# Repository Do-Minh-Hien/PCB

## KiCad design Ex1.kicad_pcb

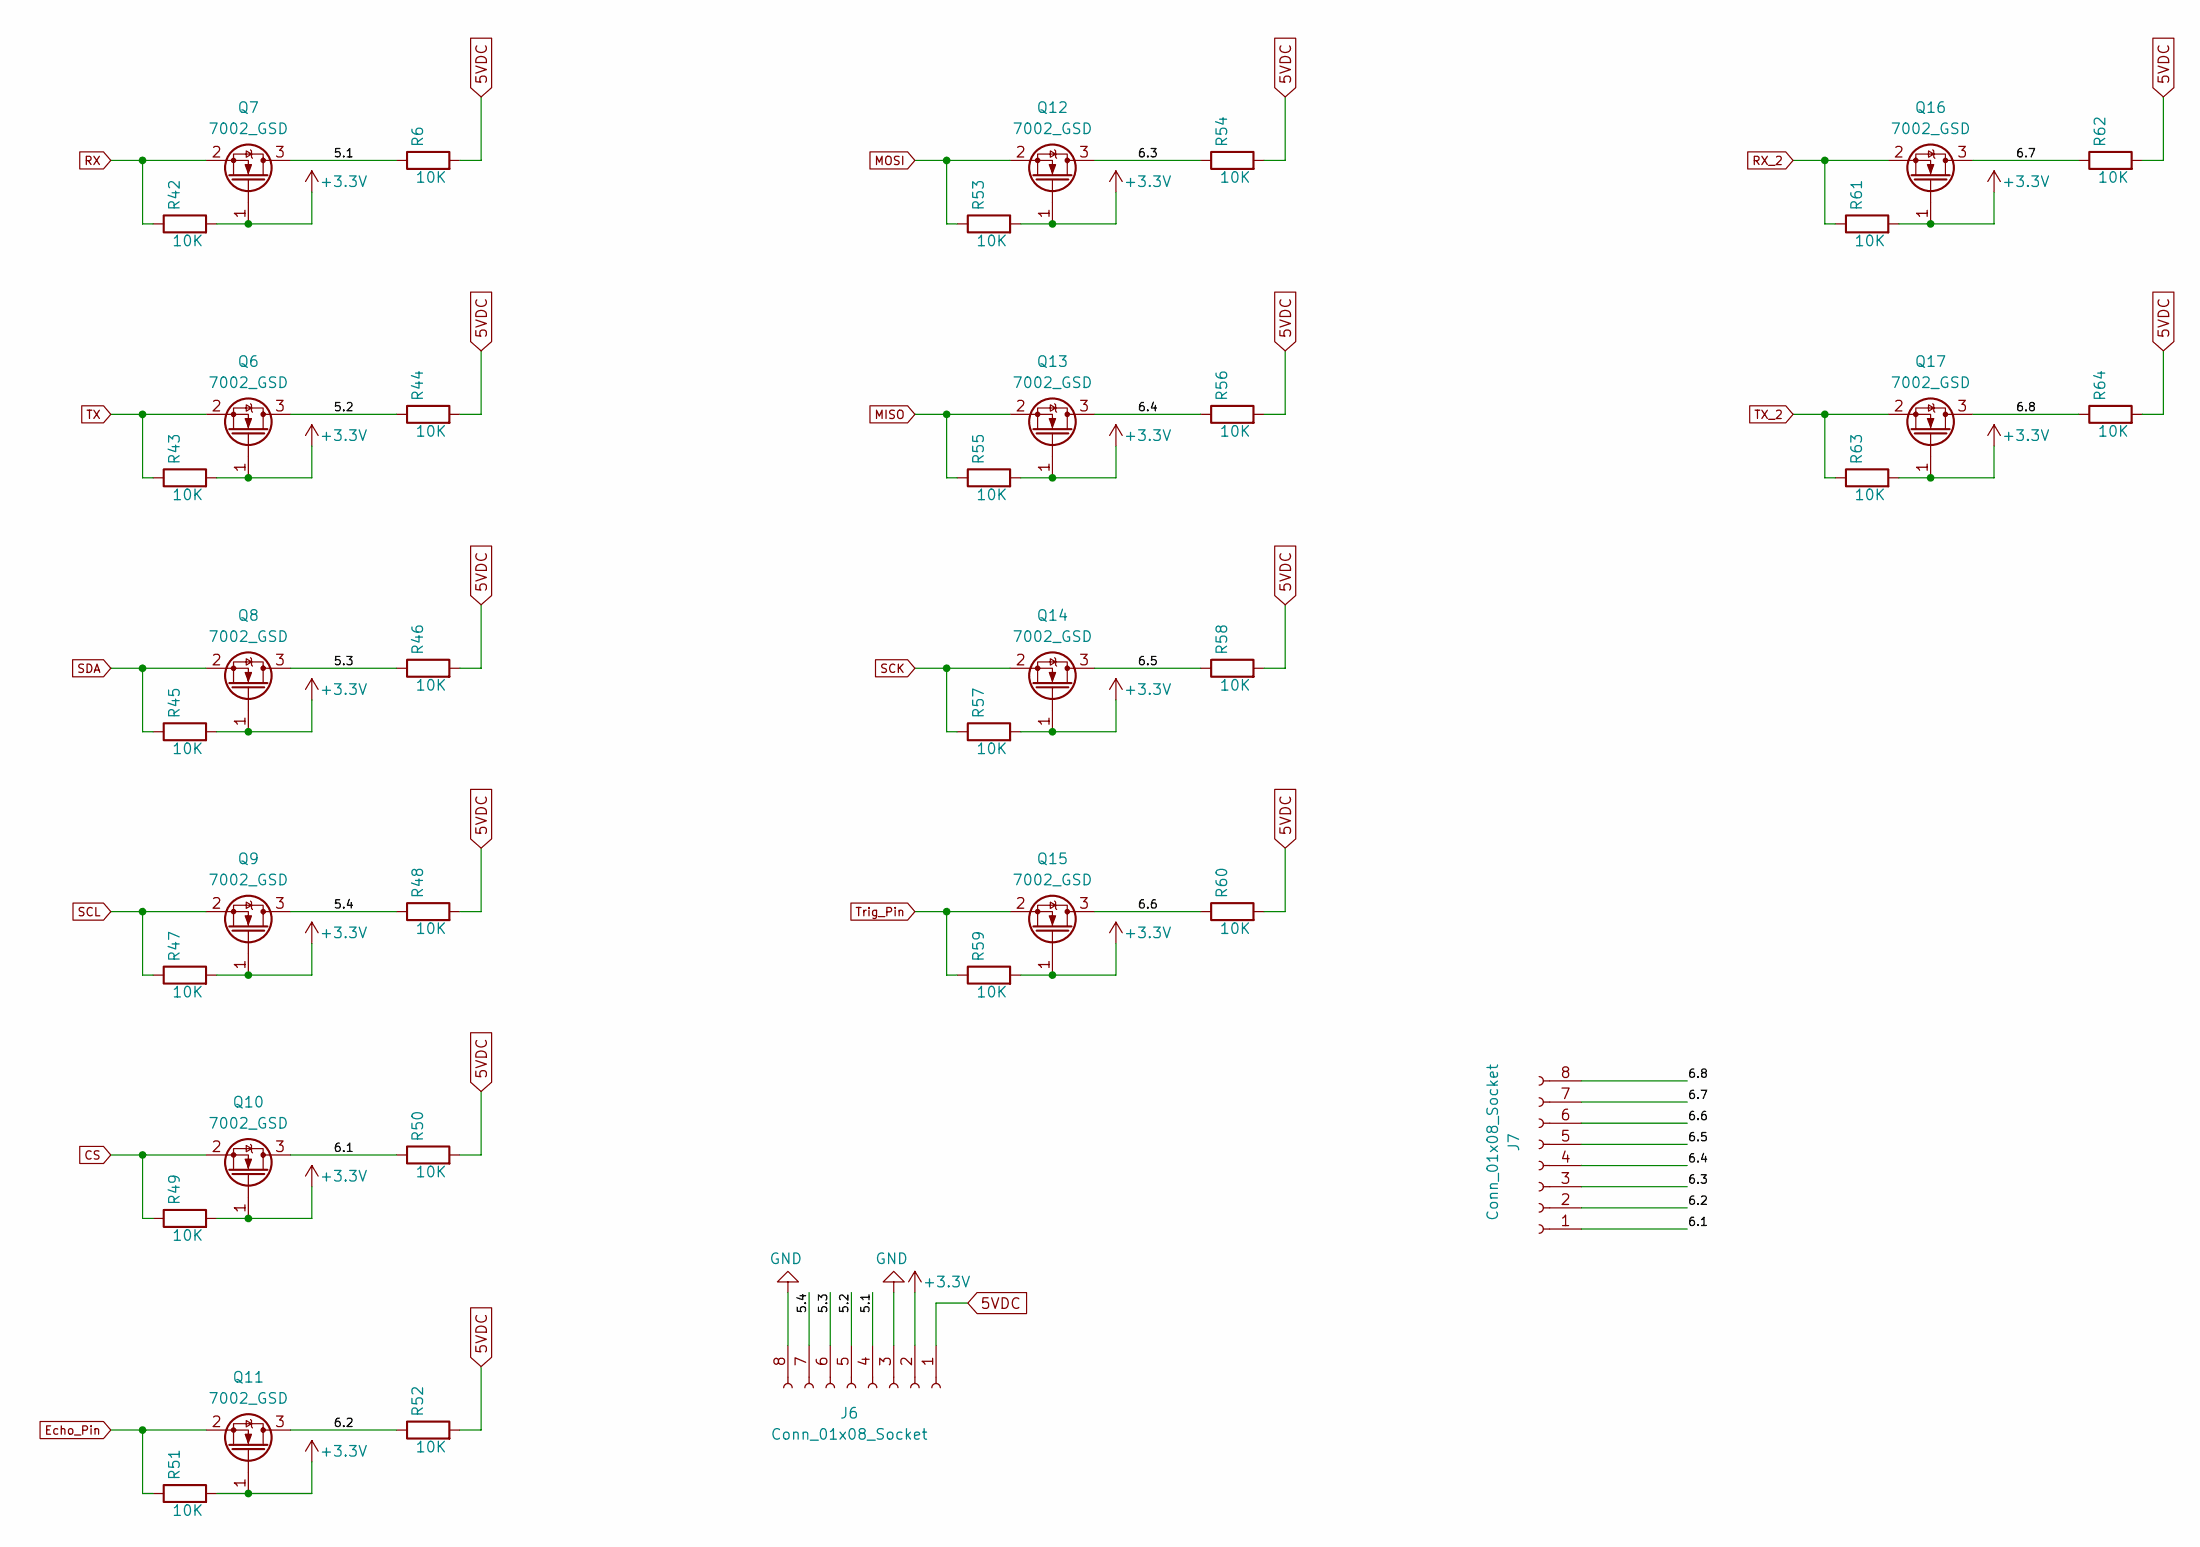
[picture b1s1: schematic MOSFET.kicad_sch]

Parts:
J6, J7: Conn_01x08_Socket; PinHeader_1x08_P2.54mm_Vertical
Q6, Q7, Q8, Q9, Q10, Q11, Q12, Q13, Q14, Q15, Q16, Q17: 7002_GSD; SOT-23
R6, R42, R43, R44, R45, R46, R47, R48, R49, R50, R51, R52, R53, R54, R55, R56, R57, R58, R59, R60, R61, R62, R63, R64: 10K; R_0603_1608Metric_Pad0.98x0.95mm_HandSolder

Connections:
0VDC: J6.3, J6.8; also elsewhere on the board
5VDC: J6.1, R6.2, R44.2, R46.2, R48.2, R50.2, R52.2, R54.2, R56.2, R58.2, R60.2, R62.2, R64.2; also elsewhere on the board
+3.3V: J6.2, Q6.1 (G), Q7.1 (G), Q8.1 (G), Q9.1 (G), Q10.1 (G), Q11.1 (G), Q12.1 (G), Q13.1 (G), Q14.1 (G), Q15.1 (G), Q16.1 (G), Q17.1 (G), R42.2, R43.2, R45.2, R47.2, R49.2, R51.2, R53.2, R55.2, R57.2, R59.2, R61.2, R63.2; also elsewhere on the board
/MOSFET/5.1: J6.4, Q7.3 (D), R6.1
/MOSFET/5.2: J6.5, Q6.3 (D), R44.1
/MOSFET/5.3: J6.6, Q8.3 (D), R46.1
/MOSFET/5.4: J6.7, Q9.3 (D), R48.1
/MOSFET/6.1: J7.1, Q10.3 (D), R50.1
/MOSFET/6.2: J7.2, Q11.3 (D), R52.1
/MOSFET/6.3: J7.3, Q12.3 (D), R54.1
/MOSFET/6.4: J7.4, Q13.3 (D), R56.1
/MOSFET/6.5: J7.5, Q14.3 (D), R58.1
/MOSFET/6.6: J7.6, Q15.3 (D), R60.1
/MOSFET/6.7: J7.7, Q16.3 (D), R62.1
/MOSFET/6.8: J7.8, Q17.3 (D), R64.1
CS: Q10.2 (S), R49.1; also elsewhere on the board
Echo_Pin: Q11.2 (S), R51.1; also elsewhere on the board
MISO: Q13.2 (S), R55.1; also elsewhere on the board
MOSI: Q12.2 (S), R53.1; also elsewhere on the board
RX: Q7.2 (S), R42.1; also elsewhere on the board
RX_2: Q16.2 (S), R61.1; also elsewhere on the board
SCK: Q14.2 (S), R57.1; also elsewhere on the board
SCL: Q9.2 (S), R47.1; also elsewhere on the board
SDA: Q8.2 (S), R45.1; also elsewhere on the board
TX: Q6.2 (S), R43.1; also elsewhere on the board
TX_2: Q17.2 (S), R63.1; also elsewhere on the board
Trig_Pin: Q15.2 (S), R59.1; also elsewhere on the board

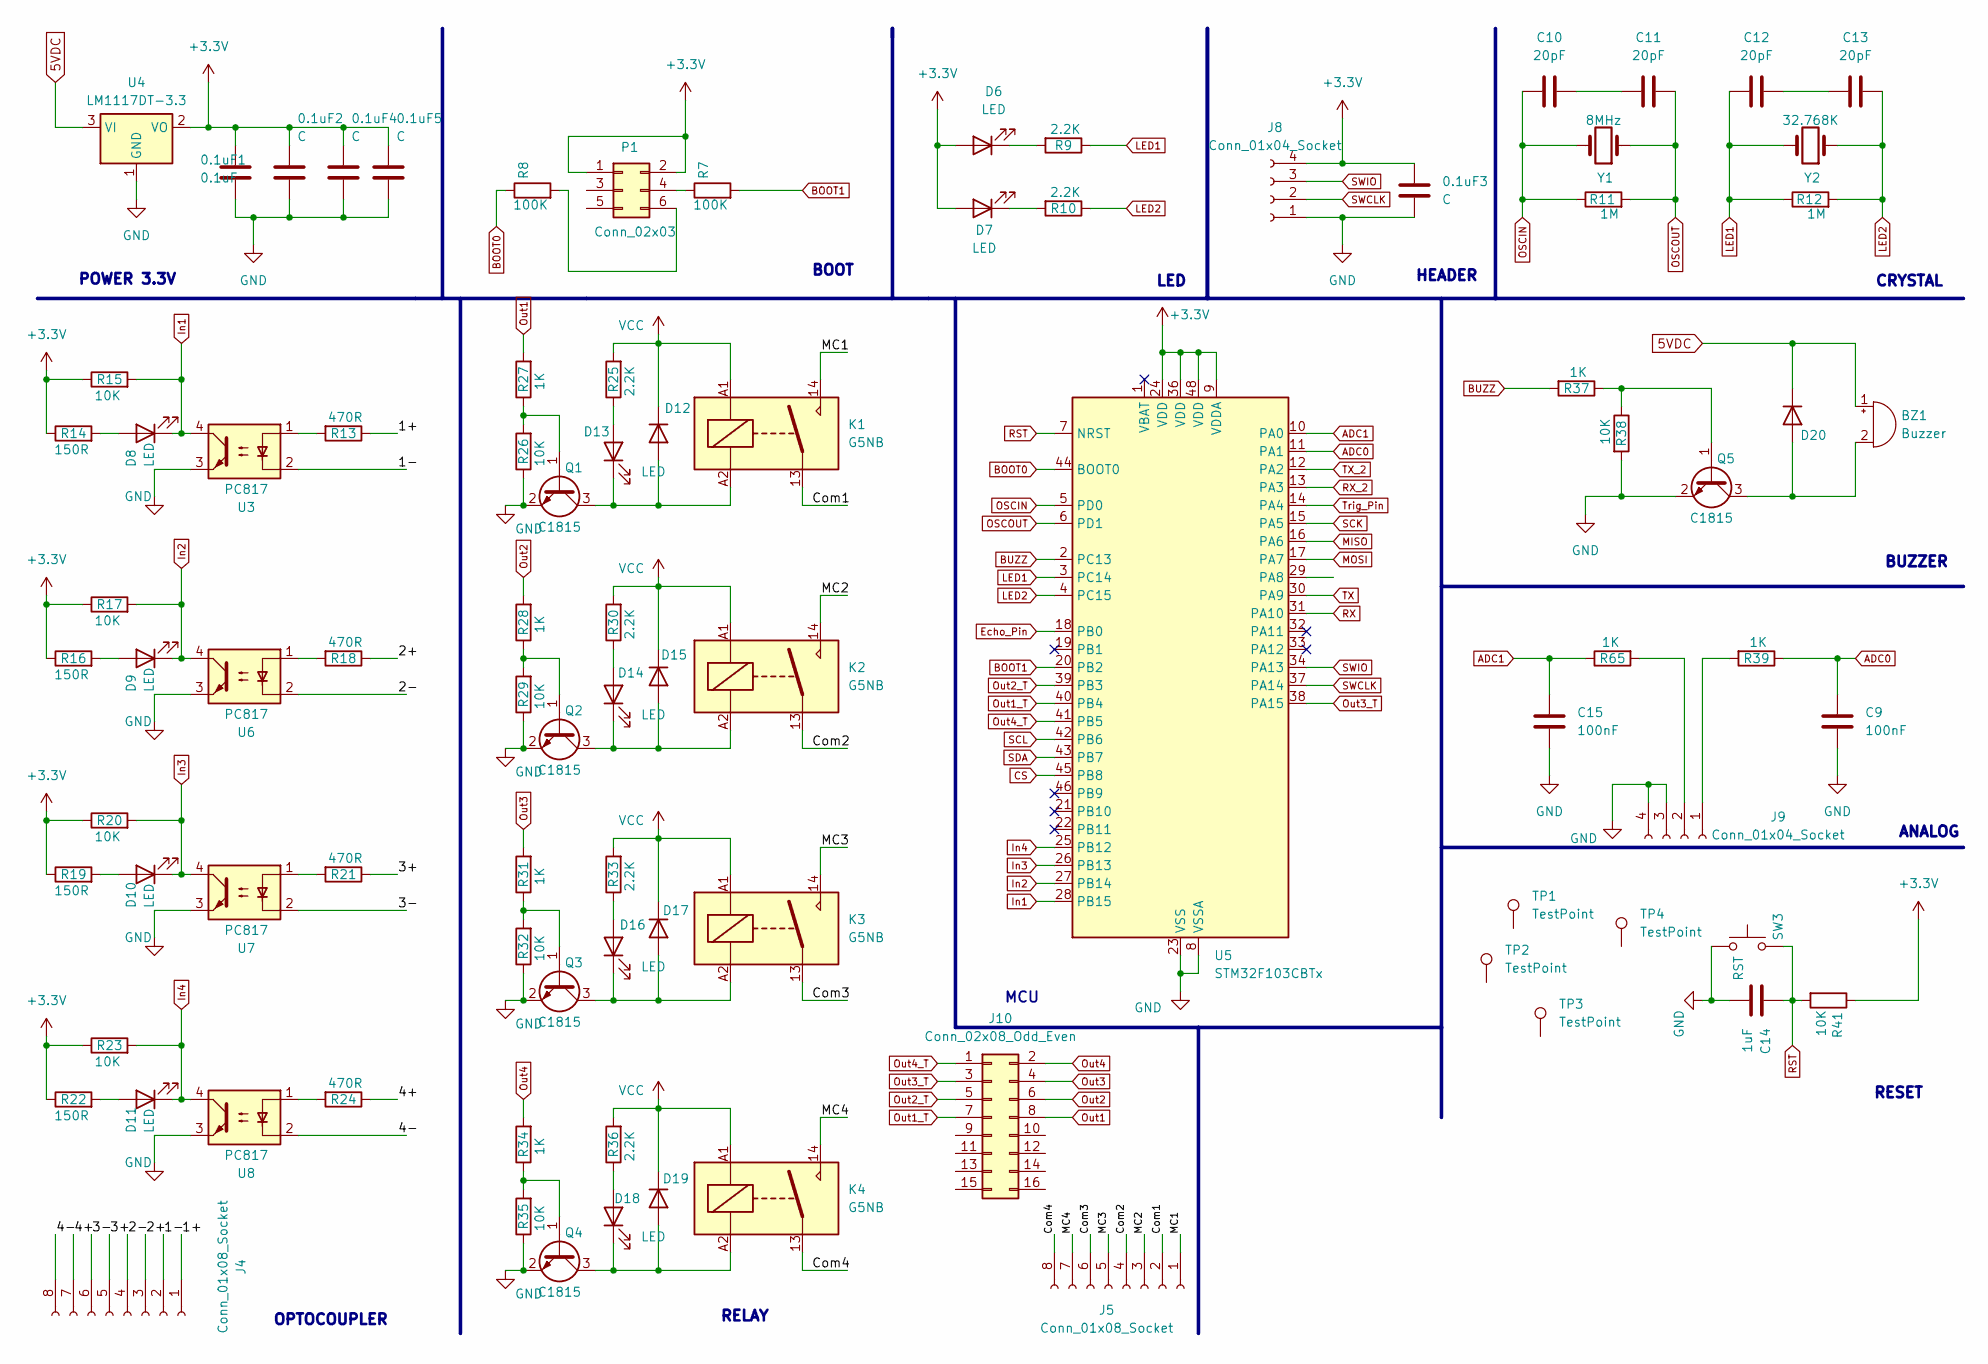
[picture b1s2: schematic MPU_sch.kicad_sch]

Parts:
0.1uF1: 0.1uF; C_0805_2012Metric_Pad1.18x1.45mm_HandSolder
0.1uF2, 0.1uF3, 0.1uF4, 0.1uF5: C; C_0805_2012Metric_Pad1.18x1.45mm_HandSolder
BZ1: Buzzer; Buzzer_12x9.5RM7.6
C9, C15: 100nF; C_0603_1608Metric_Pad1.08x0.95mm_HandSolder
C10, C11, C12, C13: 20pF; C_0603_1608Metric_Pad1.08x0.95mm_HandSolder
C14: 1uF; C_0603_1608Metric_Pad1.08x0.95mm_HandSolder
D6, D7, D8, D9, D10, D11, D13, D14, D16, D18: LED; L_0805_2012Metric_Pad1.15x1.40mm_HandSolder
D12, D15, D17, D19, D20: D; D_SMA
J4: Conn_01x08_Socket; PinHeader_1x08_P2.54mm_Vertical
J5: Conn_01x08_Socket; TerminalBlock_bornier-8_P5.08mm
J8, J9: Conn_01x04_Socket; PinHeader_1x04_P2.54mm_Vertical
J10: Conn_02x08_Odd_Even; PinHeader_2x08_P2.54mm_Vertical
K1, K2, K3, K4: G5NB; Relay_SPST_Omron_G5NB
P1: Conn_02x03; PinHeader_2x03_P2.54mm_Vertical
Q1, Q2, Q3, Q4, Q5: C1815; SOT-23
R7, R8: 100K; R_0603_1608Metric_Pad0.98x0.95mm_HandSolder
R9, R10, R25, R30, R33, R36: 2.2K; R_0805_2012Metric_Pad1.20x1.40mm_HandSolder
R11, R12: 1M; R_0603_1608Metric_Pad0.98x0.95mm_HandSolder
R13, R18, R21, R24: 470R; R_0805_2012Metric_Pad1.20x1.40mm_HandSolder
R14, R16, R19, R22: 150R; R_0805_2012Metric_Pad1.20x1.40mm_HandSolder
R15, R17, R20, R23, R26, R29, R32, R35, R38: 10K; R_0805_2012Metric_Pad1.20x1.40mm_HandSolder
R27, R28, R31, R34, R37, R39, R65: 1K; R_0805_2012Metric_Pad1.20x1.40mm_HandSolder
R41: 10K; R_0603_1608Metric_Pad0.98x0.95mm_HandSolder
SW3: RST; SW_DIP_SPSTx01_Slide_6.7x4.1mm_W6.73mm_P2.54mm_LowProfile_J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
TP1, TP2, TP3, TP4: TestPoint; TestPoint_Plated_Hole_D4.0mm
U3, U6, U7, U8: PC817; DIP-4_W7.62mm
U4: LM1117DT-3.3; TO254P470X1016X2222-3P
U5: STM32F103CBTx; LQFP-48_7x7mm_P0.5mm
Y1: 8MHz; Crystal_HC49-U_Vertical
Y2: 32.768K; Crystal_SMD_3225-4Pin_3.2x2.5mm_HandSoldering

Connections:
0VDC: 0.1uF1.2, 0.1uF2.2, 0.1uF3.2, 0.1uF4.2, 0.1uF5.2, C9.1, C14.2, C15.1, J8.1, J9.3, J9.4, Q1.2 (E), Q2.2 (E), Q3.2 (E), Q4.2 (E), Q5.2 (E), R26.1, R29.1, R32.1, R35.1, R38.2, SW3.1, U3.3, U4.1 (GND), U5.8 (VSSA), U5.23 (VSS), U5.35 (VSS), U5.47 (VSS), U6.3, U7.3, U8.3; also elsewhere on the board
5VDC: BZ1.1 (+), D20.1 (K), U4.3 (VI); also elsewhere on the board
+3.3V: 0.1uF1.1, 0.1uF2.1, 0.1uF3.1, 0.1uF4.1, 0.1uF5.1, D6.2 (A), D7.2 (A), J8.4, P1.1, P1.2, R14.1, R15.1, R16.1, R17.1, R19.1, R20.1, R22.1, R23.1, R41.1, U4.2 (VO), U5.9 (VDDA), U5.24 (VDD), U5.36 (VDD), U5.48 (VDD); also elsewhere on the board
/MPU/1+: J4.1, R13.1
/MPU/1-: J4.2, U3.2
/MPU/2+: J4.3, R18.1
/MPU/2-: J4.4, U6.2
/MPU/3+: J4.5, R21.1
/MPU/3-: J4.6, U7.2
/MPU/4+: J4.7, R24.1
/MPU/4-: J4.8, U8.2
/MPU/Com1: J5.2, K1.13
/MPU/Com2: J5.4, K2.13
/MPU/Com3: J5.6, K3.13
/MPU/Com4: J5.8, K4.13
/MPU/MC1: J5.1, K1.14
/MPU/MC2: J5.3, K2.14
/MPU/MC3: J5.5, K3.14
/MPU/MC4: J5.7, K4.14
ADC0: C9.2, R39.1, U5.11 (PA1)
ADC1: C15.2, R65.1, U5.10 (PA0)
BOOT0: R8.1, U5.44 (BOOT0)
BOOT1: R7.2, U5.20 (PB2)
BUZZ: R37.2, U5.2 (PC13)
CS: U5.45 (PB8); also elsewhere on the board
Echo_Pin: U5.18 (PB0); also elsewhere on the board
In1: D8.1 (K), R15.2, U3.4, U5.28 (PB15)
In2: D9.1 (K), R17.2, U5.27 (PB14), U6.4
In3: D10.1 (K), R20.2, U5.26 (PB13), U7.4
In4: D11.1 (K), R23.2, U5.25 (PB12), U8.4
LED1: C12.1, R9.1, R12.1, U5.3 (PC14), Y2.2
LED2: C13.2, R10.1, R12.2, U5.4 (PC15), Y2.1
MISO: U5.16 (PA6); also elsewhere on the board
MOSI: U5.17 (PA7); also elsewhere on the board
unnamed: BZ1.2 (-), D20.2 (A), Q5.3 (C)
unnamed: C10.2, C11.1
unnamed: C12.2, C13.1
unnamed: D6.1 (K), R9.2
unnamed: D7.1 (K), R10.2
unnamed: D8.2 (A), R14.2
unnamed: D9.2 (A), R16.2
unnamed: D10.2 (A), R19.2
unnamed: D11.2 (A), R22.2
unnamed: D12.2 (A), D13.1 (K), K1.A2, Q1.3 (C)
unnamed: D13.2 (A), R25.1
unnamed: D14.2 (A), R30.1
unnamed: D14.1 (K), D15.2 (A), K2.A2, Q2.3 (C)
unnamed: D16.2 (A), R33.1
unnamed: D16.1 (K), D17.2 (A), K3.A2, Q3.3 (C)
unnamed: D18.2 (A), R36.1
unnamed: D18.1 (K), D19.2 (A), K4.A2, Q4.3 (C)
unnamed: J9.1, R39.2
unnamed: J9.2, R65.2
unnamed: P1.4, R7.1
unnamed: P1.6, R8.2
unnamed: Q1.1 (B), R26.2, R27.1
unnamed: Q2.1 (B), R28.1, R29.2
unnamed: Q3.1 (B), R31.1, R32.2
unnamed: Q4.1 (B), R34.1, R35.2
unnamed: Q5.1 (B), R37.1, R38.1
unnamed: R13.2, U3.1
unnamed: R18.2, U6.1
unnamed: R21.2, U7.1
unnamed: R24.2, U8.1
OSCIN: C10.1, R11.1, U5.5 (PD0), Y1.2
OSCOUT: C11.2, R11.2, U5.6 (PD1), Y1.1
Out1: J10.8, R27.2
Out1_T: J10.7, U5.40 (PB4)
Out2: J10.6, R28.2
Out2_T: J10.5, U5.39 (PB3)
Out3: J10.4, R31.2
Out3_T: J10.3, U5.38 (PA15)
Out4: J10.2, R34.2
Out4_T: J10.1, U5.41 (PB5)
RST: C14.1, R41.2, SW3.2, U5.7 (NRST)
RX: U5.31 (PA10); also elsewhere on the board
RX_2: U5.13 (PA3); also elsewhere on the board
SCK: U5.15 (PA5); also elsewhere on the board
SCL: U5.42 (PB6); also elsewhere on the board
SDA: U5.43 (PB7); also elsewhere on the board
SWCLK: J8.2, U5.37 (PA14)
SWIO: J8.3, U5.34 (PA13)
TX: U5.30 (PA9); also elsewhere on the board
TX_2: U5.12 (PA2); also elsewhere on the board
Trig_Pin: U5.14 (PA4); also elsewhere on the board
VCC: D12.1 (K), D15.1 (K), D17.1 (K), D19.1 (K), K1.A1, K2.A1, K3.A1, K4.A1, R25.2, R30.2, R33.2, R36.2; also elsewhere on the board

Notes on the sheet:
BUZZER
HEADER
RESET
LED
OPTOCOUPLER
ANALOG
RELAY
MCU
BOOT
POWER 3.3V
CRYSTAL

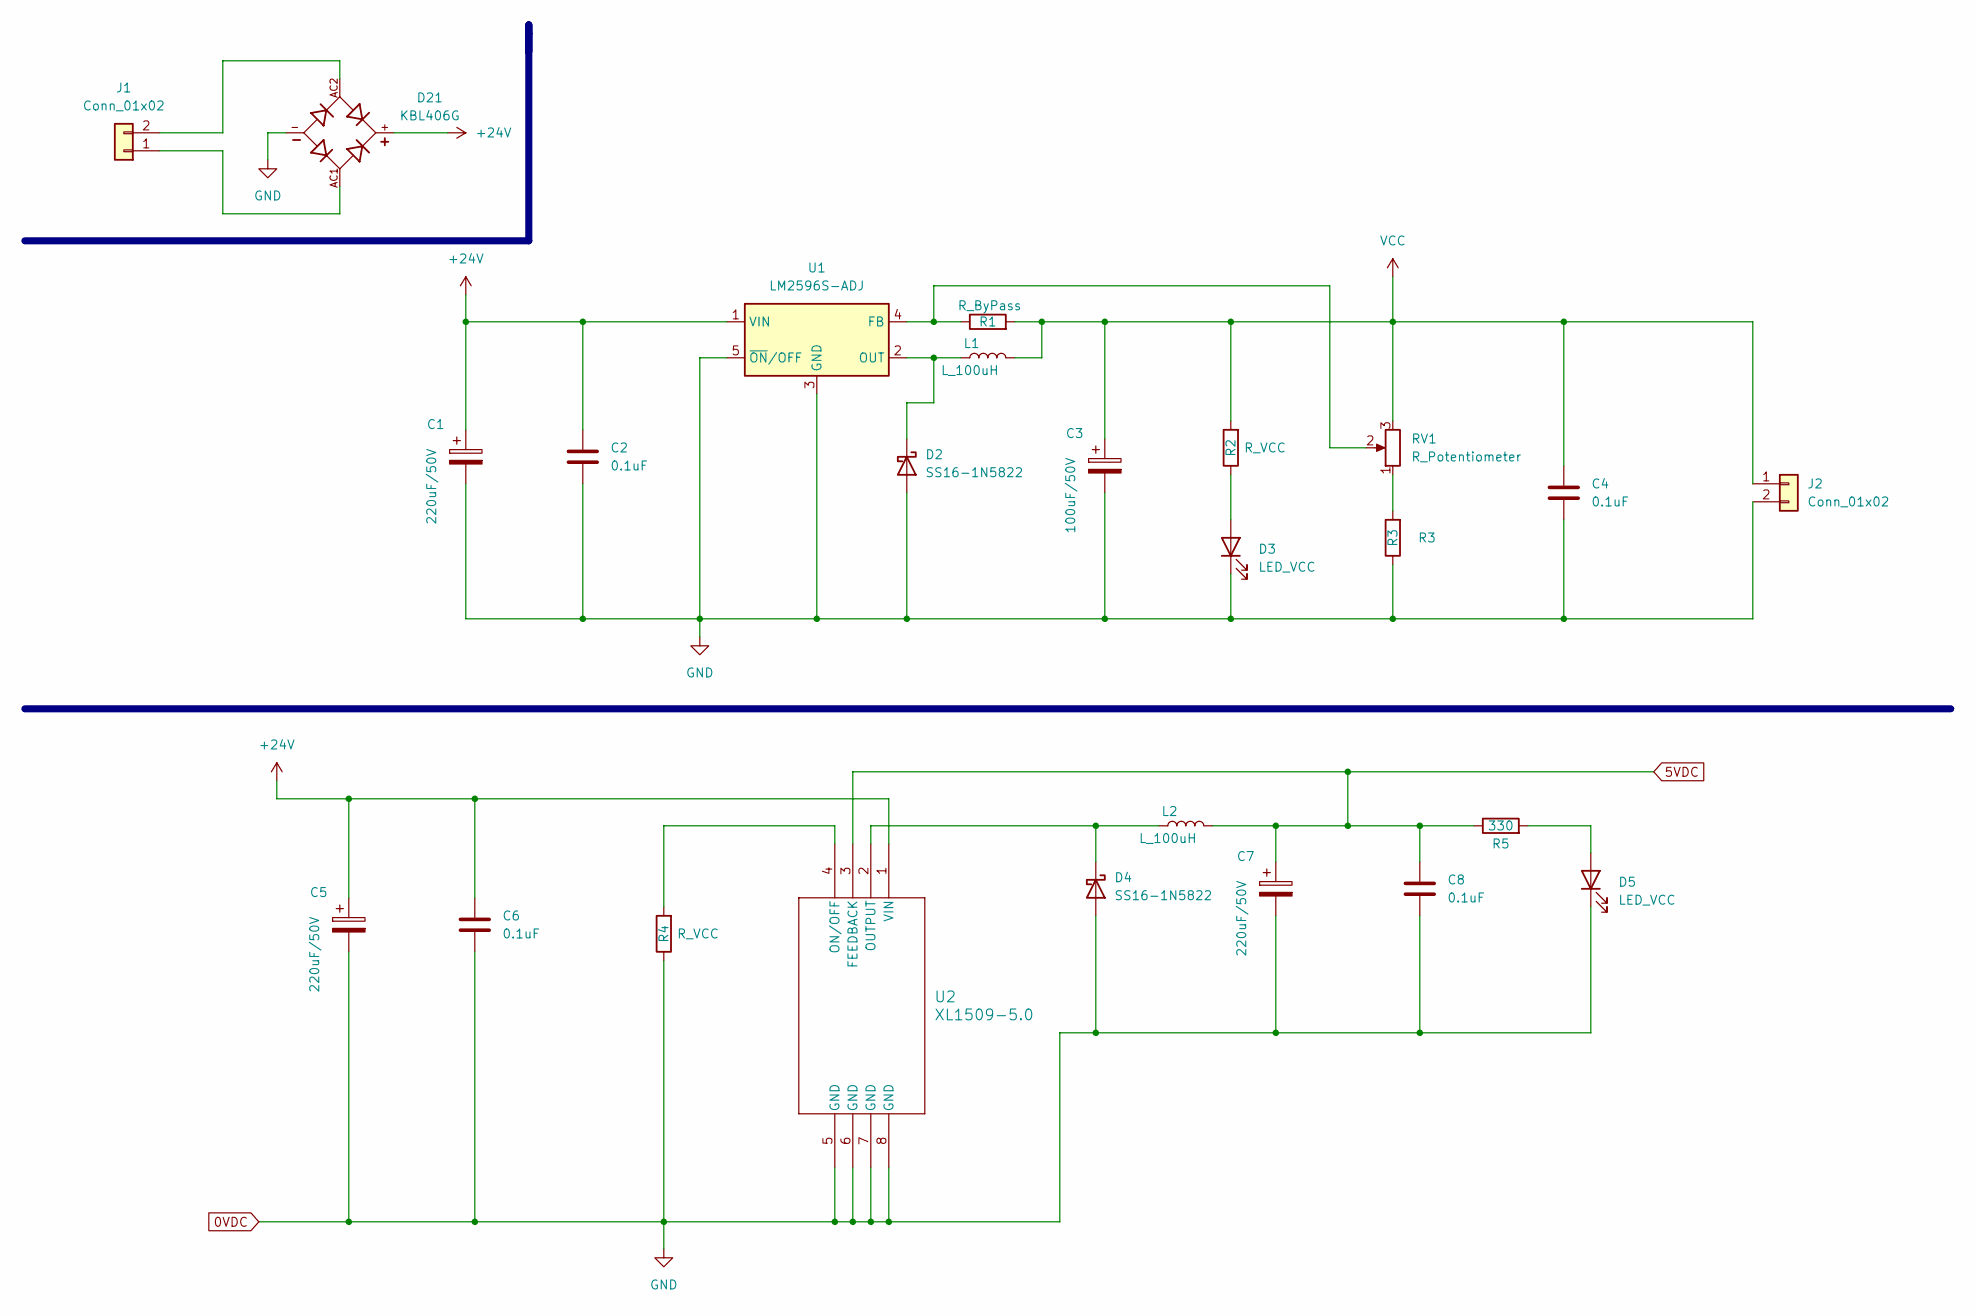
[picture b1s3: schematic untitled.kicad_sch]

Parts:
C1, C5, C7: 220uF/50V; CP_Radial_D8.0mm_P3.80mm
C2, C4, C6, C8: 0.1uF; C_0805_2012Metric_Pad1.18x1.45mm_HandSolder
C3: 100uF/50V; CP_Radial_D8.0mm_P3.80mm
D2, D4: SS16-1N5822; D_DO-201AD_P15.24mm_Horizontal
D3, D5: LED_VCC; L_0805_2012Metric_Pad1.15x1.40mm_HandSolder
D21: KBL406G; SIP600W130P510L1900H1630Q4; PARTREV I2103
J1, J2: Conn_01x02; TerminalBlock_bornier-2_P5.08mm
L1, L2: L_100uH; L_Toroid_Vertical_L14.7mm_W8.6mm_P5.58mm_Pulse_KM-1
R1: R_ByPass; R_0805_2012Metric
R2: R_VCC; R_0805_2012Metric_Pad1.20x1.40mm_HandSolder
R3: R3; R_0805_2012Metric
R4: R_VCC; R_0805_2012Metric
R5: 330; R_0805_2012Metric
RV1: R_Potentiometer; Potentiometer_Bourns_3296W_Vertical
U1: LM2596S-ADJ; TO-263-5_TabPin3
U2: XL1509-5.0; SOP-8_3.76x4.96mm_P1.27mm

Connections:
0VDC: C1.2, C2.2, C3.2, C4.2, C5.2, C6.2, C7.2, C8.2, D2.2 (A), D3.1 (K), D4.2 (A), D5.1 (K), D21.-, J2.2, R3.1, R4.1, U1.3 (GND), U1.5 (~ON/OFF), U2.5 (GND), U2.6 (GND), U2.7 (GND), U2.8 (GND); also elsewhere on the board
5VDC: C7.1, C8.1, L2.2, R5.1, U2.3 (FEEDBACK); also elsewhere on the board
+24V: C1.1, C2.1, C5.1, C6.1, D21.+, U1.1 (VIN), U2.1 (VIN)
unnamed: D2.1 (K), L1.1, U1.2 (OUT)
unnamed: D3.2 (A), R2.1
unnamed: D4.1 (K), L2.1, U2.2 (OUTPUT)
unnamed: D5.2 (A), R5.2
unnamed: D21.AC1, J1.1
unnamed: D21.AC2, J1.2
unnamed: R3.2, RV1.1
unnamed: R1.1, RV1.2, U1.4 (FB)
unnamed: R4.2, U2.4 (ON/OFF)
VCC: C3.1, C4.1, J2.1, L1.2, R1.2, R2.2, RV1.3; also elsewhere on the board

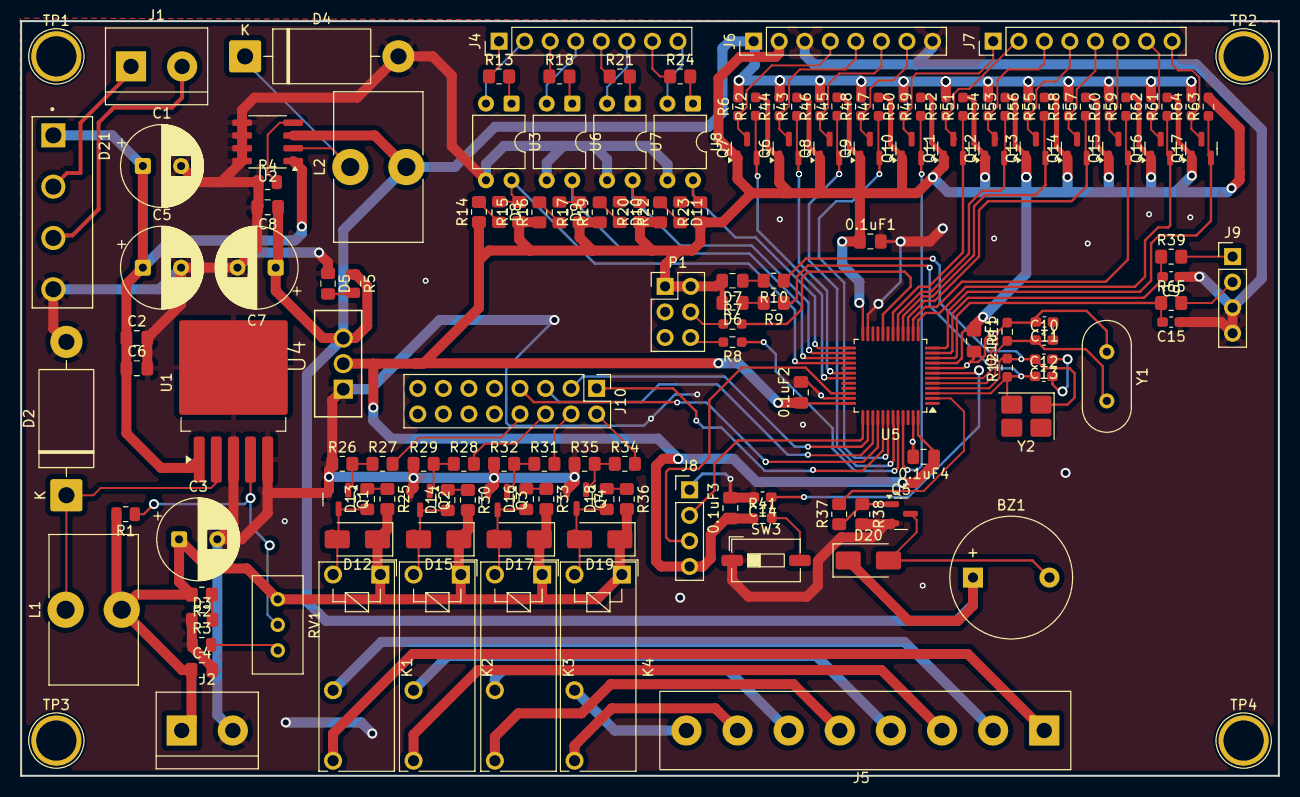
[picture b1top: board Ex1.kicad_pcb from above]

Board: 2 copper layers, 125.0 x 75.0 mm, 154 parts (0 on the bottom side), 108 nets.

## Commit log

2025-08-13 PCB Project
2025-08-14 sdfas
